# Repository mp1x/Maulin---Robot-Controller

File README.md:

# Maulin---Robot-Controller
This project is a custom ESP32-based robotics controller designed for dual DC motors, quadrature encoders, an MPU6050 IMU, SSD1306 OLED display, emergency stop system, and battery monitoring. The project includes a full KiCad schematic, PCB layout, Wokwi simulation, and ESP32 firmware.

This project is not a robot itself, however, it is the electronics that power a robot, the complete control system that acts as the robot’s brain. Instead of building wheels or a chassis, this project focuses on designing a universal robotics controller built around the ESP32, capable of driving motors, reading quadrature encoders, processing IMU data, handling emergency stop safety, monitoring battery voltage, and displaying system information on an OLED dashboard. The controller integrates all the core functions real robots rely on internally: motion tracking, speed and distance measurement, drift correction, orientation sensing, and safety logic. This board can be mounted onto any future robot—rovers, line followers, balancing robots, robotic arms, or any system that needs precise motor control and feedback. In short, this project builds the brain, not the body, forming a professional foundation for future robotics development.

## Wokwi Simulation
This project includes a full Wokwi simulation of the ESP32, OLED, IMU, and encoders.

Simulation link: https://wokwi.com/projects/468589263635231745

## Project Files
- /schematic — KiCad schematic + PNG/PDF
- /pcb — PCB layout screenshots + 3D view
- /firmware — ESP32 code
- /wokwi — Simulation files

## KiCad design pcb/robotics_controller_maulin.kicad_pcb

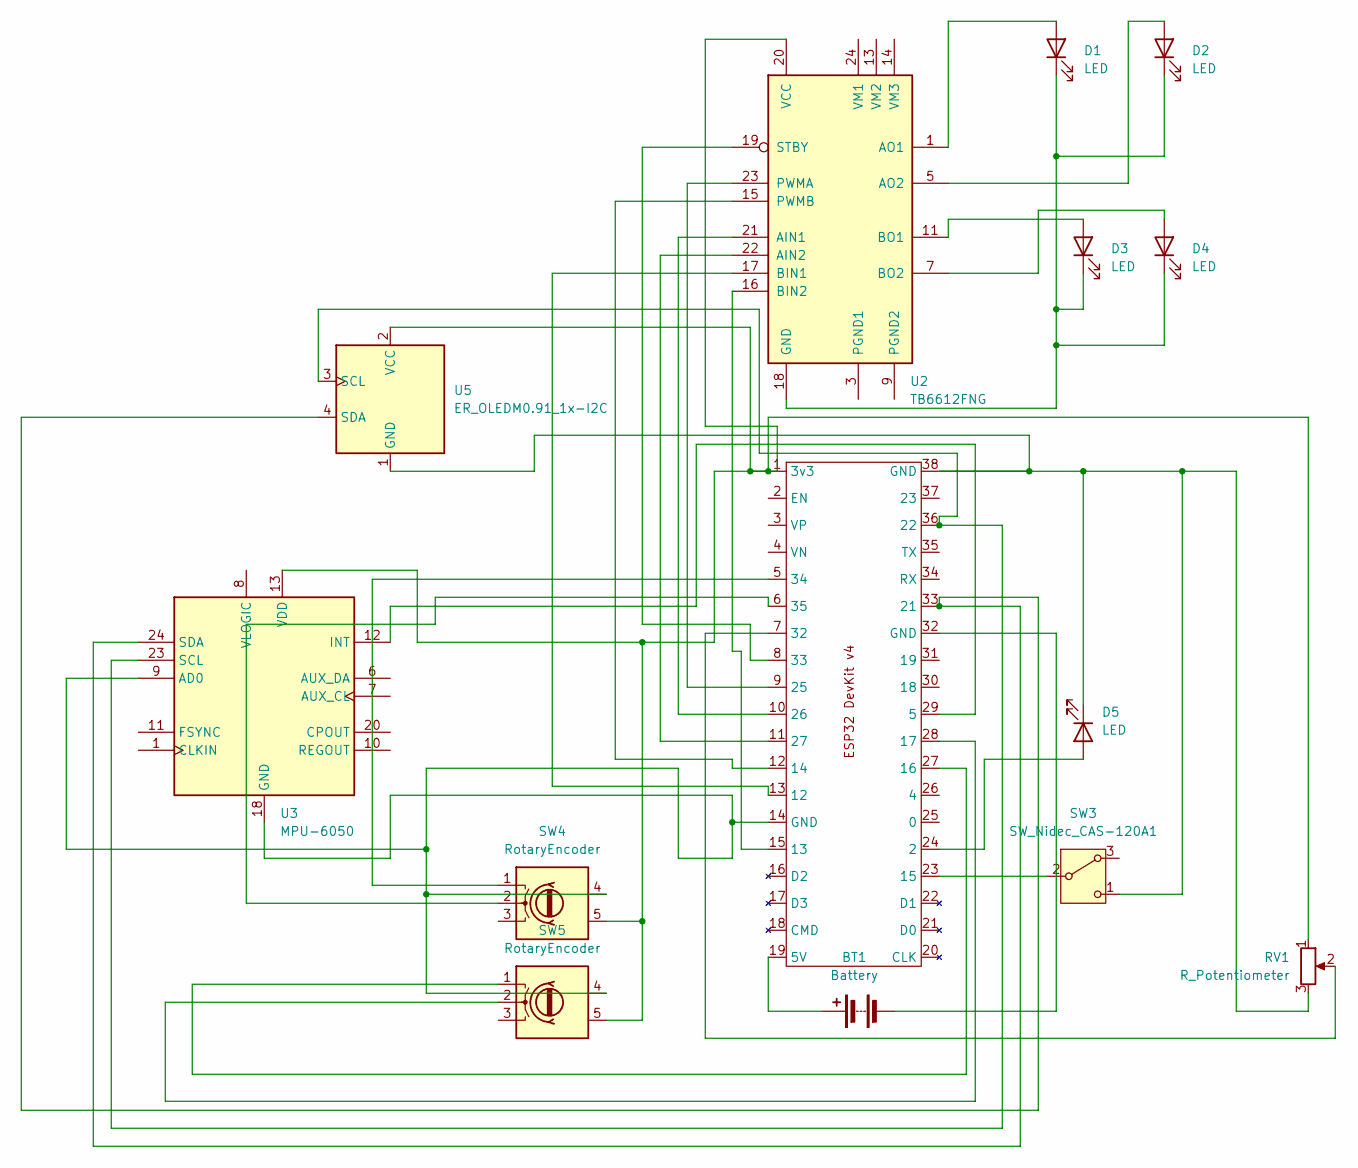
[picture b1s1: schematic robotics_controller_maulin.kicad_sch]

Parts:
BT1: Battery; BatteryHolder_Keystone_2460_1xAA
D1, D3: LED; LED_D3.0mm_IRBlack
D2, D4: LED; LED_D3.0mm_IRGrey
D5: LED; LED_D5.0mm_Horizontal_O1.27mm_Z3.0mm_IRGrey
RV1: R_Potentiometer; Potentiometer_ACP_CA6-VSMD_Vertical
SW3: SW_Nidec_CAS-120A1; Nidec_Copal_CAS-120A
SW4, SW5: RotaryEncoder; PinHeader_1x05_P2.54mm_Vertical
U2: TB6612FNG; SSOP-24_5.3x8.2mm_P0.65mm
U3: MPU-6050; InvenSense_QFN-24_4x4mm_P0.5mm
U4: ESP32-DevKitC-V4-b
U5: ER_OLEDM0.91_1x-I2C

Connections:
unnamed: BT1.1 (+), U4.19 (5V)
unnamed: BT1.2 (-), U4.32 (GND)
unnamed: D1.2 (A), U2.1 (AO1), U2.2 (AO1)
unnamed: D1.1 (K), D2.1 (K), D3.1 (K), D4.1 (K), U2.18 (GND)
unnamed: D2.2 (A), U2.5 (AO2), U2.6 (AO2)
unnamed: D3.2 (A), U2.11 (BO1), U2.12 (BO1)
unnamed: D4.2 (A), U2.7 (BO2), U2.8 (BO2)
unnamed: D5.2 (A), U4.24 (2)
unnamed: D5.1 (K), RV1.3, SW3.1 (C), U4.38 (GND), U5.1 (GND)
unnamed: SW3.2 (B), U4.23 (15)
unnamed: SW4.1 (CLK), U4.5 (34)
unnamed: SW4.2 (DT), U4.6 (35)
unnamed: SW4.4 (GND), SW5.4 (GND), U3.9 (AD0), U3.18 (GND), U4.14 (GND)
unnamed: RV1.1, SW4.5 (VCC), SW5.5 (VCC), U2.20 (VCC), U3.13 (VDD), U4.1 (3v3), U5.2 (VCC)
unnamed: SW5.1 (CLK), U4.27 (16)
unnamed: SW5.2 (DT), U4.28 (17)
unnamed: U2.21 (AIN1), U4.10 (26)
unnamed: U2.22 (AIN2), U4.11 (27)
unnamed: U2.17 (BIN1), U4.13 (12)
unnamed: U2.16 (BIN2), U4.15 (13)
unnamed: U2.3 (PGND1), U2.4 (PGND1)
unnamed: U2.9 (PGND2), U2.10 (PGND2)
unnamed: U2.23 (PWMA), U4.9 (25)
unnamed: U2.15 (PWMB), U4.12 (14)
unnamed: U2.19 (STBY), U4.8 (33)
unnamed: U3.12 (INT), U4.29 (5)
unnamed: U3.23 (SCL), U4.36 (22), U5.3 (SCL)
unnamed: U3.24 (SDA), U4.33 (21), U5.4 (SDA)
unnamed: RV1.2, U4.7 (32)

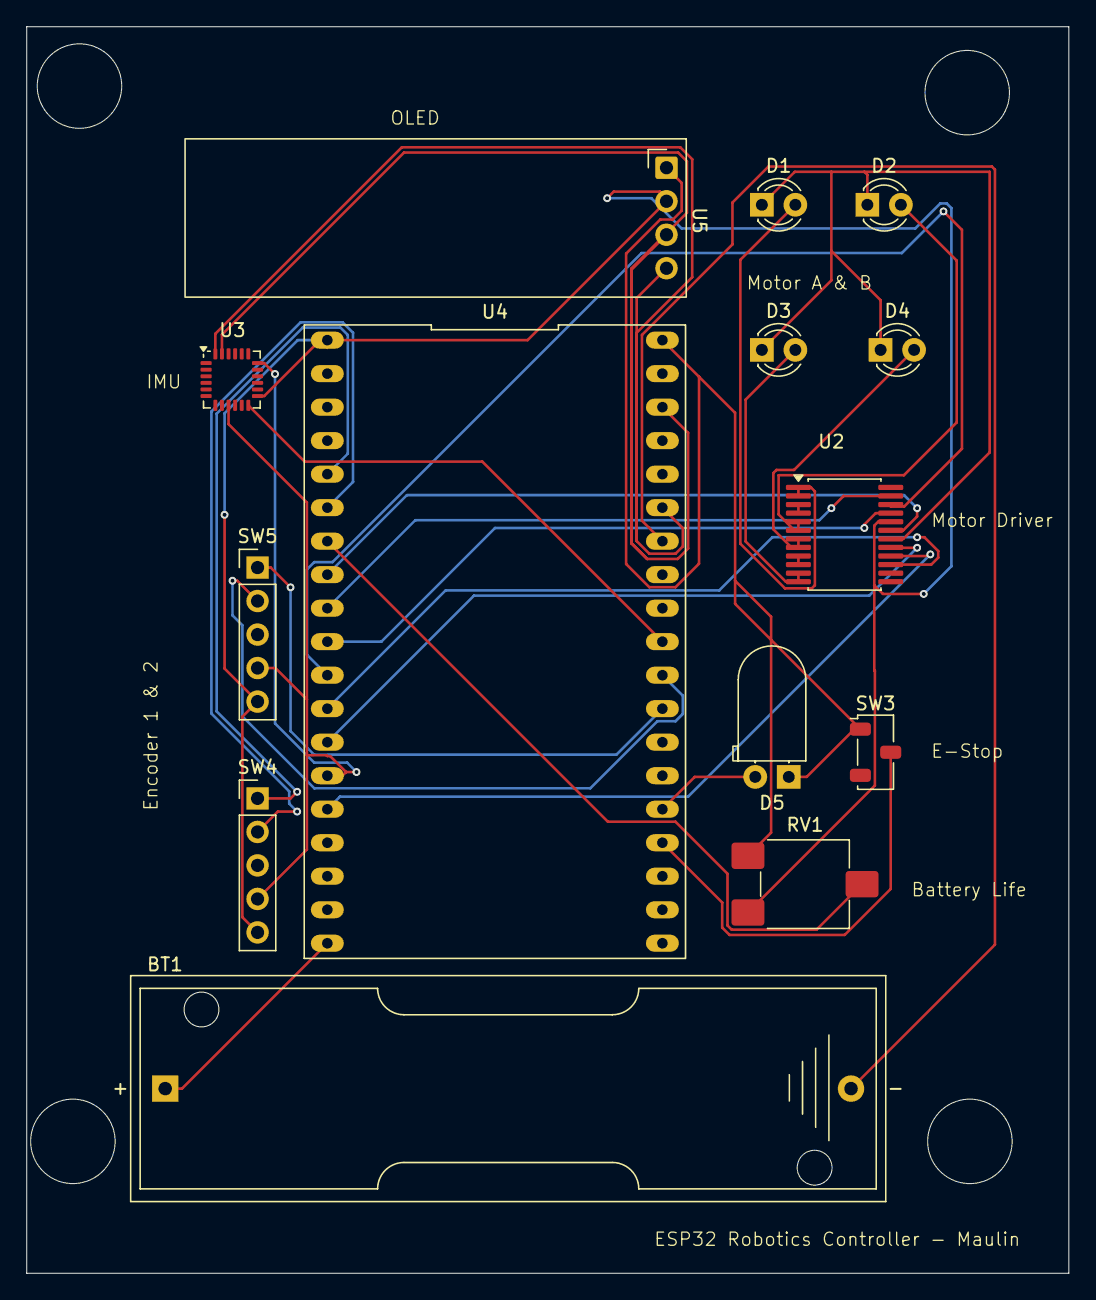
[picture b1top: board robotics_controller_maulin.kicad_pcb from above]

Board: 2 copper layers, 79.0 x 94.5 mm, 14 parts (0 on the bottom side), 29 nets.
